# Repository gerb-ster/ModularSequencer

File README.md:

# Modular Sequencer

A modular sequencer consisting of a control module and 1 or more linkable io-modules. Al daisychained together.

## Notes

- All connected by a parallel SPI bus.
- contains 1 serial connected line for discovery
- a termination jumper for the last io-board
- all io-boards start up in a discovery mode
- if io board has termination jumper it sends signal
- control boards send an ID which is registered by io board
- io board goes out of discovery mode and sets discovery line high
- this triggers the same process in the ajasoned io-board module
- this goes on until control board senses a discovery line high
- play mode is then activated
- control board sends a gate active command; board_id + port + on / off
- io board scans inputs, gate on/off, cv value & gate length for all of its 4 ports and sends it to the control board.

## features

### Main Control Board

- tempo pot
- tempo external input (bpm)
- tempo CV input (?)
- start / stop button
- start / stop trigger inputs (?)
- CV output
- CV Portamento
- Gate Output

### IO Board

- 4x CV level pot
- 4x Gate length pot
- 4x Gate on/off toggle switch
- 4x Step indicator LED

## Links

https://www.instructables.com/ATTiny84-I2C-Slave-Arduino-UNO/
https://thecustomizewindows.com/2019/03/how-to-invert-signal-for-arduino-high-to-low-or-the-reverse/
https://docs.arduino.cc/learn/communication/wire

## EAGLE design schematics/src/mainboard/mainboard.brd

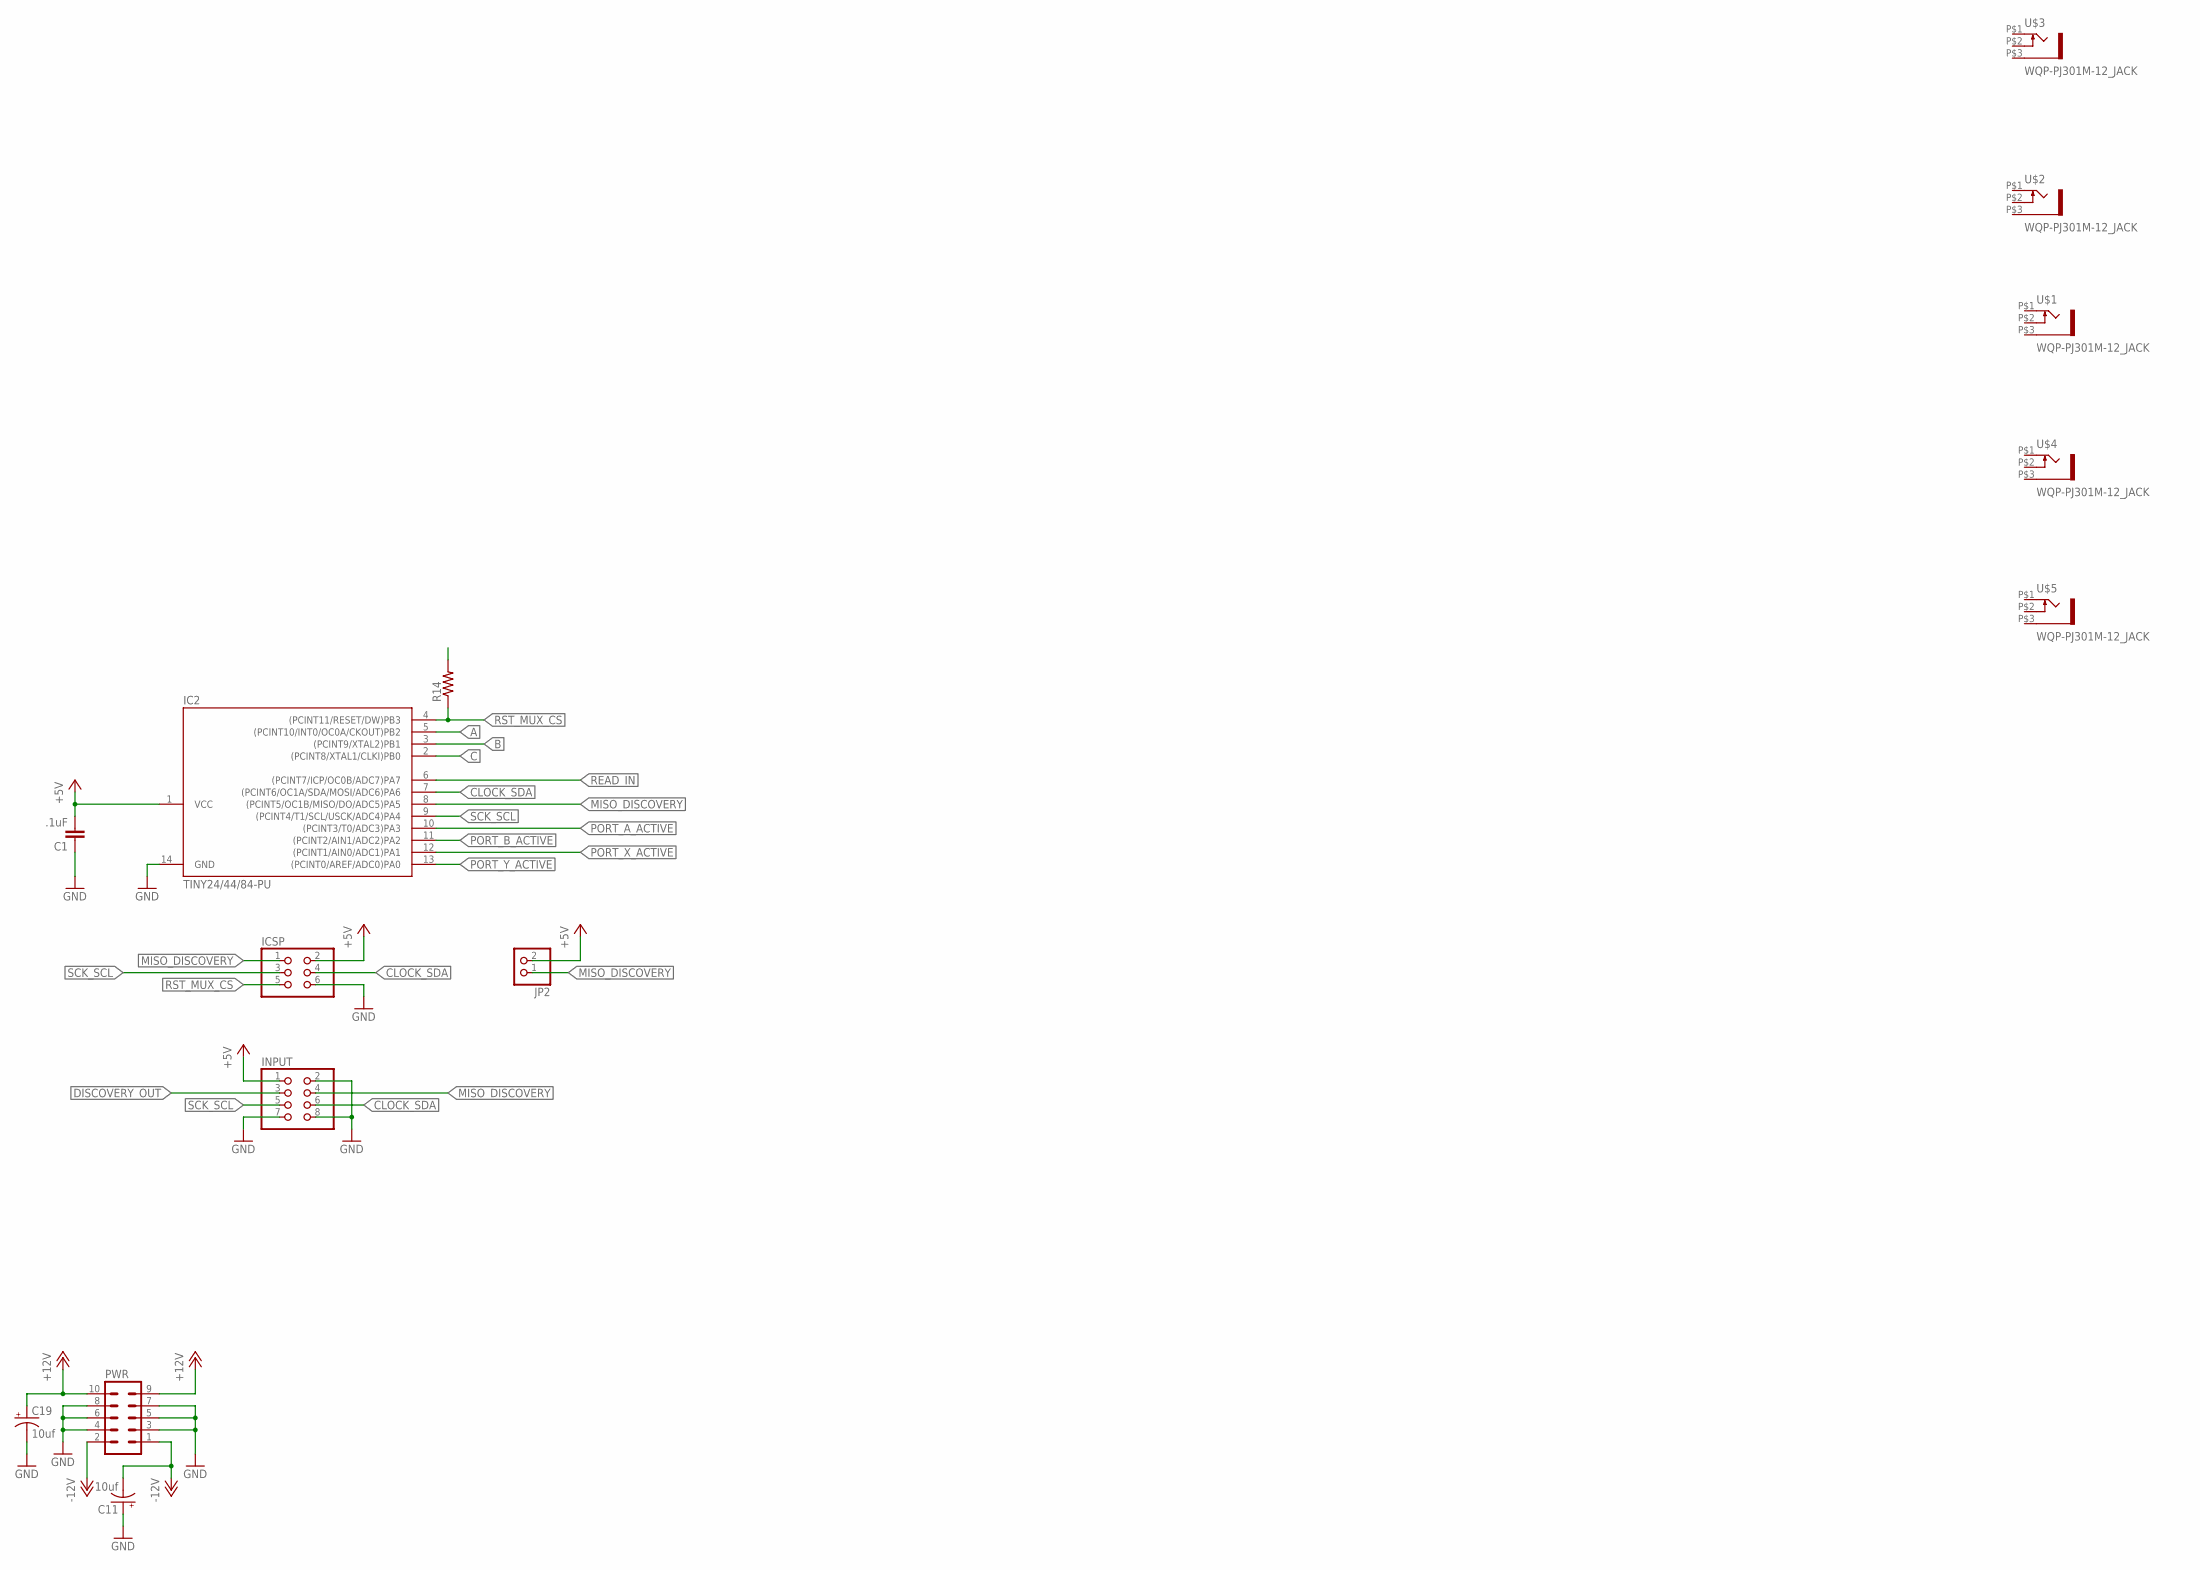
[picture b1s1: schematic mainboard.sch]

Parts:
C1: .1uF; C050-024X044
C11, C19: 10uf; E2,5-5
IC2: TINY24/44/84-PU; DIL14
ICSP: PINHD-2X3; 2X03
INPUT: PINHD-2X4; 2X04
JP2: PINHD-1X2; 1X02
PWR: ML10
R14: R-US_0204/7; 0204/7
U$1, U$2, U$3, U$4, U$5: WQP-PJ301M-12_JACK

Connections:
+5V: C1.2, IC2.1 (VCC), ICSP.2, INPUT.1, JP2.2, R14.2
+12V: C19.+, PWR.9, PWR.10
-12V: C11.-, PWR.1, PWR.2
A: IC2.5 ((PCINT10/INT0/OC0A/CKOUT)PB2)
B: IC2.3 ((PCINT9/XTAL2)PB1)
C: IC2.2 ((PCINT8/XTAL1/CLKI)PB0)
CLOCK_SDA: IC2.7 ((PCINT6/OC1A/SDA/MOSI/ADC6)PA6), ICSP.4, INPUT.6
DISCOVERY_OUT: INPUT.3
GND: C1.1, C11.+, C19.-, IC2.14 (GND), ICSP.6, INPUT.2, INPUT.7, INPUT.8, PWR.3, PWR.4, PWR.5, PWR.6, PWR.7, PWR.8
MISO_DISCOVERY: IC2.8 ((PCINT5/OC1B/MISO/DO/ADC5)PA5), ICSP.1, INPUT.4, JP2.1
PORT_A_ACTIVE: IC2.10 ((PCINT3/T0/ADC3)PA3)
PORT_B_ACTIVE: IC2.11 ((PCINT2/AIN1/ADC2)PA2)
PORT_X_ACTIVE: IC2.12 ((PCINT1/AIN0/ADC1)PA1)
PORT_Y_ACTIVE: IC2.13 ((PCINT0/AREF/ADC0)PA0)
READ_IN: IC2.6 ((PCINT7/ICP/OC0B/ADC7)PA7)
RST_MUX_CS: IC2.4 ((PCINT11/RESET/DW)PB3), ICSP.5, R14.1
SCK_SCL: IC2.9 ((PCINT4/T1/SCL/USCK/ADC4)PA4), ICSP.3, INPUT.5

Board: 2 copper layers, 14 parts (0 on the bottom side), 8 nets, no tracks yet.

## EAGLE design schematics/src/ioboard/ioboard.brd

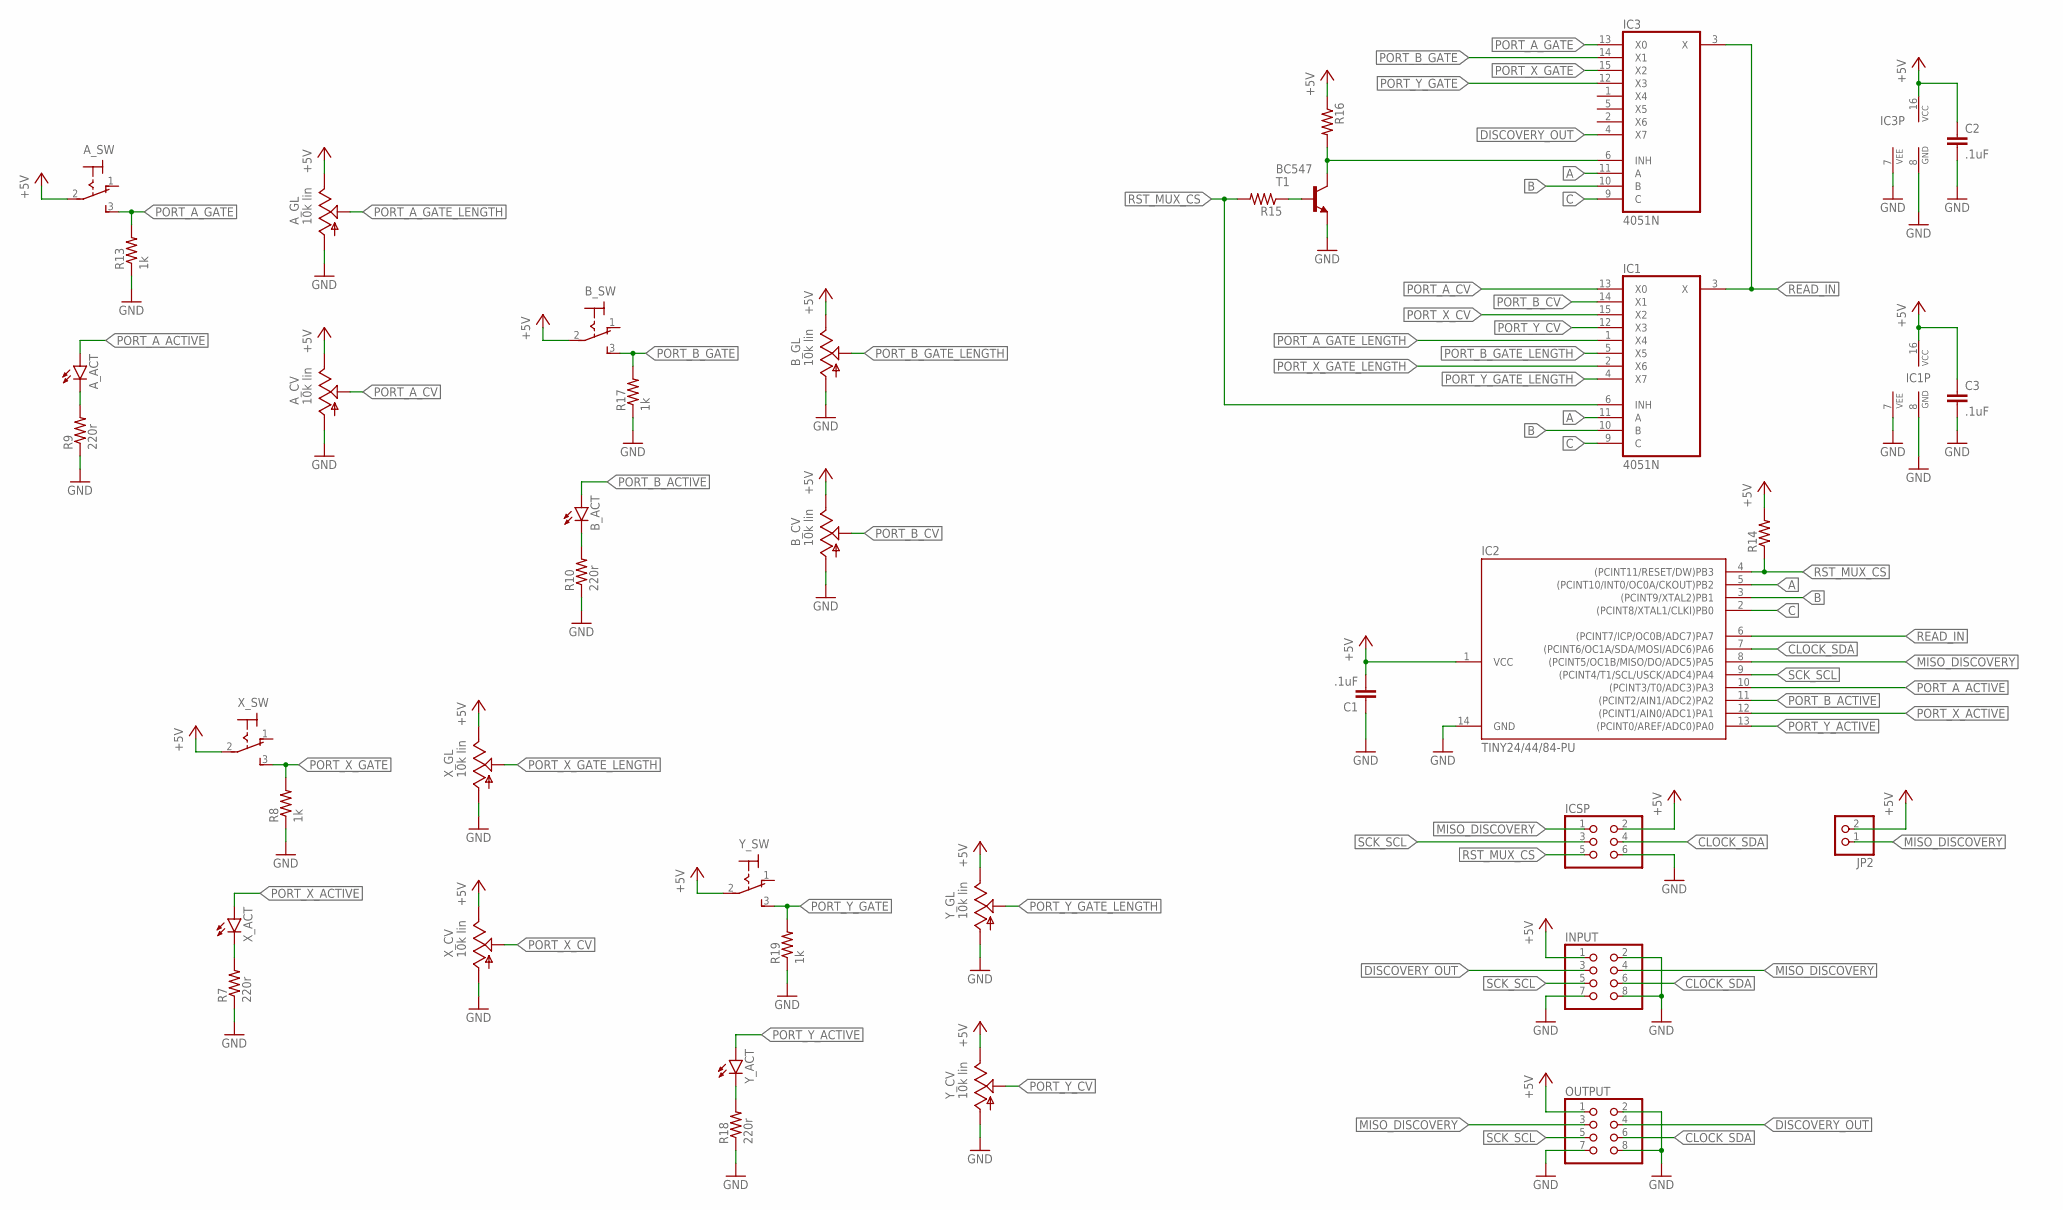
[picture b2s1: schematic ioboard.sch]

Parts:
A_ACT: LED5MM
A_CV: 10k lin; EVUF
A_GL: 10k lin; EVUF
A_SW: M9040P
B_ACT: LED5MM
B_CV: 10k lin; EVUF
B_GL: 10k lin; EVUF
B_SW: M9040P
C1, C2, C3: .1uF; C050-024X044
IC1, IC3: 4051N; DIL16
IC2: TINY24/44/84-PU; DIL14
ICSP: PINHD-2X3; 2X03
INPUT: PINHD-2X4; 2X04
JP2: PINHD-1X2; 1X02
OUTPUT: PINHD-2X4; 2X04
R7, R9, R10, R18: 220r; 0204/7
R8, R13, R17, R19: 1k; 0204/7
R14, R15, R16: R-US_0204/7; 0204/7
T1: BC547; TO92
X_ACT: LED5MM
X_CV: 10k lin; EVUF
X_GL: 10k lin; EVUF
X_SW: M9040P
Y_ACT: LED5MM
Y_CV: 10k lin; EVUF
Y_GL: 10k lin; EVUF
Y_SW: M9040P

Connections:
+5V: A_CV.3 (E), A_GL.3 (E), A_SW.2, B_CV.3 (E), B_GL.3 (E), B_SW.2, C1.2, C2.1, C3.1, IC1.16 (VCC), IC2.1 (VCC), IC3.16 (VCC), ICSP.2, INPUT.1, JP2.2, OUTPUT.1, R14.2, R16.1, X_CV.3 (E), X_GL.3 (E), X_SW.2, Y_CV.3 (E), Y_GL.3 (E), Y_SW.2
A: IC1.11 (A), IC2.5 ((PCINT10/INT0/OC0A/CKOUT)PB2), IC3.11 (A)
B: IC1.10 (B), IC2.3 ((PCINT9/XTAL2)PB1), IC3.10 (B)
C: IC1.9 (C), IC2.2 ((PCINT8/XTAL1/CLKI)PB0), IC3.9 (C)
CLOCK_SDA: IC2.7 ((PCINT6/OC1A/SDA/MOSI/ADC6)PA6), ICSP.4, INPUT.6, OUTPUT.6
DISCOVERY_OUT: IC3.4 (X7), INPUT.3, OUTPUT.4
GND: A_CV.1 (A), A_GL.1 (A), B_CV.1 (A), B_GL.1 (A), C1.1, C2.2, C3.2, IC1.7 (VEE), IC1.8 (GND), IC2.14 (GND), IC3.7 (VEE), IC3.8 (GND), ICSP.6, INPUT.2, INPUT.7, INPUT.8, OUTPUT.2, OUTPUT.7, OUTPUT.8, R7.1, R8.1, R9.1, R10.1, R13.1, R17.1, R18.1, R19.1, T1.1 (E), X_CV.1 (A), X_GL.1 (A), Y_CV.1 (A), Y_GL.1 (A)
MISO_DISCOVERY: IC2.8 ((PCINT5/OC1B/MISO/DO/ADC5)PA5), ICSP.1, INPUT.4, JP2.1, OUTPUT.3
unnamed: A_ACT.K (C), R9.2
unnamed: B_ACT.K (C), R10.2
unnamed: R15.1, T1.2 (B)
unnamed: R7.2, X_ACT.K (C)
unnamed: R18.2, Y_ACT.K (C)
unnamed: IC3.6 (INH), R16.2, T1.3 (C)
PORT_A_ACTIVE: A_ACT.A, IC2.10 ((PCINT3/T0/ADC3)PA3)
PORT_A_CV: A_CV.2 (S), IC1.13 (X0)
PORT_A_GATE: A_SW.3 (S), IC3.13 (X0), R13.2
PORT_A_GATE_LENGTH: A_GL.2 (S), IC1.1 (X4)
PORT_B_ACTIVE: B_ACT.A, IC2.11 ((PCINT2/AIN1/ADC2)PA2)
PORT_B_CV: B_CV.2 (S), IC1.14 (X1)
PORT_B_GATE: B_SW.3 (S), IC3.14 (X1), R17.2
PORT_B_GATE_LENGTH: B_GL.2 (S), IC1.5 (X5)
PORT_X_ACTIVE: IC2.12 ((PCINT1/AIN0/ADC1)PA1), X_ACT.A
PORT_X_CV: IC1.15 (X2), X_CV.2 (S)
PORT_X_GATE: IC3.15 (X2), R8.2, X_SW.3 (S)
PORT_X_GATE_LENGTH: IC1.2 (X6), X_GL.2 (S)
PORT_Y_ACTIVE: IC2.13 ((PCINT0/AREF/ADC0)PA0), Y_ACT.A
PORT_Y_CV: IC1.12 (X3), Y_CV.2 (S)
PORT_Y_GATE: IC3.12 (X3), R19.2, Y_SW.3 (S)
PORT_Y_GATE_LENGTH: IC1.4 (X7), Y_GL.2 (S)
READ_IN: IC1.3 (X), IC2.6 ((PCINT7/ICP/OC0B/ADC7)PA7), IC3.3 (X)
RST_MUX_CS: IC1.6 (INH), IC2.4 ((PCINT11/RESET/DW)PB3), ICSP.5, R14.1, R15.2
SCK_SCL: IC2.9 ((PCINT4/T1/SCL/USCK/ADC4)PA4), ICSP.3, INPUT.5, OUTPUT.5

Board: 2 copper layers, 38 parts (0 on the bottom side), 33 nets, no tracks yet.

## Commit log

2022-05-03 notes added
2022-05-04 Fixed schematics & descriptions
2022-05-17 Updated Firmware
2022-05-18 Updated Faceplates
2022-05-18 Fixed issues
2022-05-21 Fixed schematics
2022-05-28 General updates
